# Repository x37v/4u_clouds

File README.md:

# 4u_clouds
a 4u layout for the mutable instrument's clouds, with added SD capability?

http://mutable-instruments.net/modules/clouds/open

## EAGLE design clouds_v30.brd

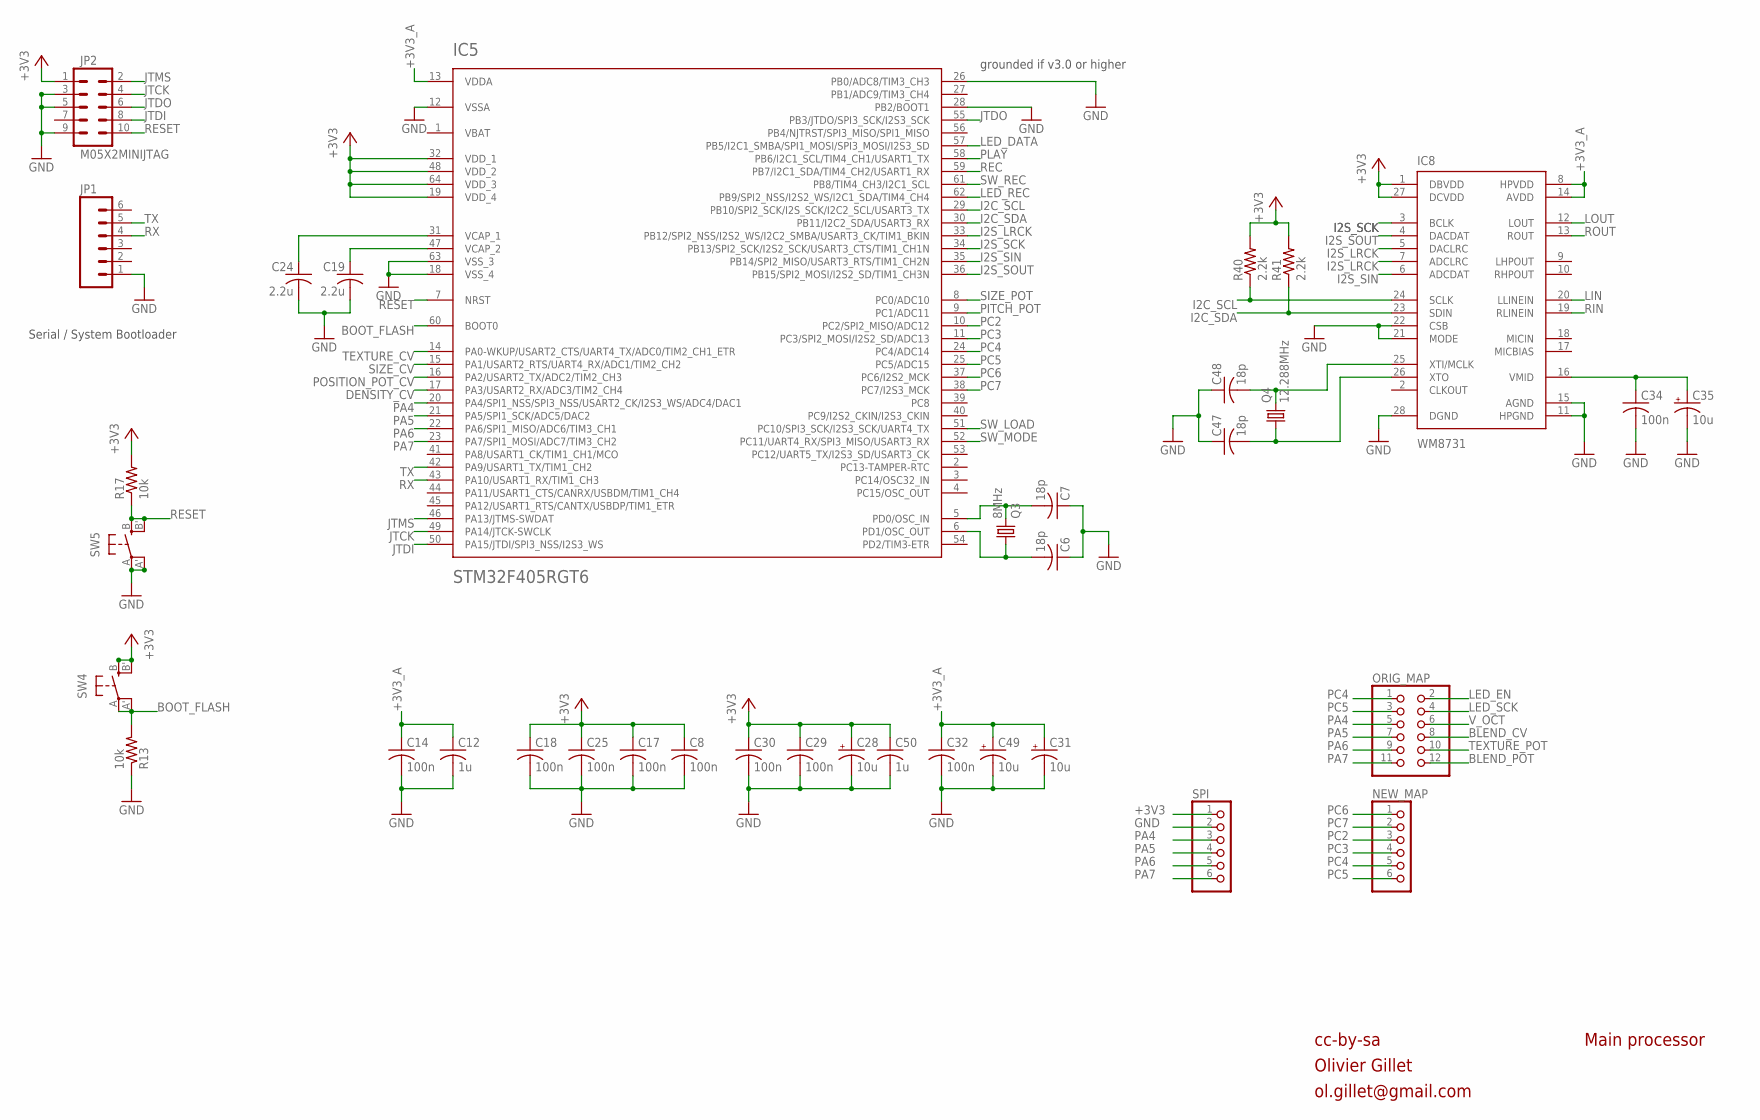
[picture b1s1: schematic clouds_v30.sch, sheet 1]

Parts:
C6, C7, C47, C48: 18p; C0603
C8, C14, C17, C18, C25, C29, C30, C32, C34: 100n; C0603
C12, C50: 1u; C0603
C19, C24: 2.2u; C0805
C28, C49: 10u; PANASONIC_A
C31, C35: 10u; PANASONIC_B
IC5: STM32F405RGT6; TQFP-10X10-64
IC8: WM8731; SSOP28
JP1: M06SIP; 1X06
JP2: M05X2MINIJTAG; 2X5-1.27
NEW_MAP: PINHD-1X6; 1X06
ORIG_MAP: PINHD-2X6; 2X06
Q3: 8MHz; HC49UP
Q4: 12.288MHz; HC49UP
R13, R17: 10k; R0603
R40, R41: 2.2k; R0603
SPI: PINHD-1X6; 1X06
SW4, SW5: EVQQ2; EVQ-Q2

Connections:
+3V3: C8.1, C17.1, C18.1, C25.1, C28.+, C29.1, C30.1, C50.1, IC5.19 (VDD_4), IC5.32 (VDD_1), IC5.48 (VDD_2), IC5.64 (VDD_3), IC8.1 (DBVDD), IC8.27 (DCVDD), JP2.1, R17.2, R40.2, R41.2, SPI.1, SW4.B (S), SW4.B' (S1); also elsewhere on the board
+3V3_A: C12.1, C14.1, C31.+, C32.1, C49.+, IC5.13 (VDDA), IC8.8 (HPVDD), IC8.14 (AVDD); also elsewhere on the board
BLEND_CV: ORIG_MAP.8; also elsewhere on the board
BLEND_POT: ORIG_MAP.12; also elsewhere on the board
BOOT_FLASH: IC5.60 (BOOT0), R13.2, SW4.A, SW4.A' (P1)
DENSITY_CV: IC5.17 (PA3/USART2_RX/ADC3/TIM2_CH4); also elsewhere on the board
GND: C6.1, C7.1, C8.2, C12.2, C14.2, C17.2, C18.2, C19.2, C24.2, C25.2, C28.-, C29.2, C30.2, C31.-, C32.2, C34.2, C35.-, C47.1, C48.1, C49.-, C50.2, IC5.12 (VSSA), IC5.18 (VSS_4), IC5.26 (PB0/ADC8/TIM3_CH3), IC5.28 (PB2/BOOT1), IC5.63 (VSS_3), IC8.11 (HPGND), IC8.15 (AGND), IC8.21 (MODE), IC8.22 (CSB), IC8.28 (DGND), JP1.1, JP2.3, JP2.5, JP2.9, R13.1, SPI.2, SW5.A, SW5.A' (P1); also elsewhere on the board
I2C_SCL: IC5.29 (PB10/SPI2_SCK/I2S_SCK/I2C2_SCL/USART3_TX), IC8.24 (SCLK), R40.1
I2C_SDA: IC5.30 (PB11/I2C2_SDA/USART3_RX), IC8.23 (SDIN), R41.1
I2S_LRCK: IC5.33 (PB12/SPI2_NSS/I2S2_WS/I2C2_SMBA/USART3_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), IC8.5 (DACLRC), IC8.7 (ADCLRC)
I2S_SCK: IC5.34 (PB13/SPI2_SCK/I2S2_SCK/USART3_CTS/TIM1_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), IC8.3 (BCLK)
I2S_SIN: IC5.35 (PB14/SPI2_MISO/USART3_RTS/TIM1_CH2N), IC8.6 (ADCDAT)
I2S_SOUT: IC5.36 (PB15/SPI2_MOSI/I2S2_SD/TIM1_CH3N), IC8.4 (DACDAT)
JTCK: IC5.49 (PA14/JTCK-SWCLK), JP2.4
JTDI: IC5.50 (PA15/JTDI/SPI3_NSS/I2S3_WS), JP2.8
JTDO: IC5.55 (PB3/JTDO/SPI3_SCK/I2S3_SCK), JP2.6
JTMS: IC5.46 (PA13/JTMS-SWDAT), JP2.2
LED_DATA: IC5.57 (PB5/I2C1_SMBA/SPI1_MOSI/SPI3_MOSI/I2S3_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); also elsewhere on the board
LED_EN: ORIG_MAP.2; also elsewhere on the board
LED_REC: IC5.62 (PB9/SPI2_NSS/I2S2_WS/I2C1_SDA/TIM4_CH4); also elsewhere on the board
LED_SCK: ORIG_MAP.4; also elsewhere on the board
LIN: IC8.20 (LLINEIN); also elsewhere on the board
LOUT: IC8.12 (LOUT); also elsewhere on the board
unnamed: C7.2, IC5.5 (PD0/OSC_IN), Q3.2
unnamed: C6.2, IC5.6 (PD1/OSC_OUT), Q3.1
unnamed: C19.1, IC5.47 (VCAP_2)
unnamed: C34.1, C35.+, IC8.16 (VMID)
unnamed: C24.1, IC5.31 (VCAP_1)
unnamed: C47.2, IC8.26 (XTO), Q4.1
unnamed: C48.2, IC8.25 (XTI/MCLK), Q4.2
PA4: IC5.20 (PA4/SPI1_NSS/SPI3_NSS/USART2_CK/I2S3_WS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), ORIG_MAP.5, SPI.3
PA5: IC5.21 (PA5/SPI1_SCK/ADC5/DAC2), ORIG_MAP.7, SPI.4
PA6: IC5.22 (PA6/SPI1_MISO/ADC6/TIM3_CH1), ORIG_MAP.9, SPI.5
PA7: IC5.23 (PA7/SPI1_MOSI/ADC7/TIM3_CH2), ORIG_MAP.11, SPI.6
PC2: IC5.10 (PC2/SPI2_MISO/ADC12), NEW_MAP.3
PC3: IC5.11 (PC3/SPI2_MOSI/I2S2_SD/ADC13), NEW_MAP.4
PC4: IC5.24 (PC4/ADC14), NEW_MAP.5, ORIG_MAP.1
PC5: IC5.25 (PC5/ADC15), NEW_MAP.6, ORIG_MAP.3
PC6: IC5.37 (PC6/I2S2_MCK), NEW_MAP.1
PC7: IC5.38 (PC7/I2S3_MCK), NEW_MAP.2
PITCH_POT: IC5.9 (PC1/ADC11); also elsewhere on the board
PLAY: IC5.58 (PB6/I2C1_SCL/TIM4_CH1/USART1_TX); also elsewhere on the board
POSITION_POT_CV: IC5.16 (PA2/USART2_TX/ADC2/TIM2_CH3); also elsewhere on the board
REC: IC5.59 (PB7/I2C1_SDA/TIM4_CH2/USART1_RX); also elsewhere on the board
RESET: IC5.7 (NRST), JP2.10, R17.1, SW5.B (S), SW5.B' (S1)
RIN: IC8.19 (RLINEIN); also elsewhere on the board
ROUT: IC8.13 (ROUT); also elsewhere on the board
RX: IC5.43 (PA10/USART1_RX/TIM1_CH3), JP1.4
SIZE_CV: IC5.15 (PA1/USART2_RTS/UART4_RX/ADC1/TIM2_CH2); also elsewhere on the board
SIZE_POT: IC5.8 (PC0/ADC10); also elsewhere on the board
SW_LOAD: IC5.51 (PC10/SPI3_SCK/I2S3_SCK/UART4_TX); also elsewhere on the board
SW_MODE: IC5.52 (PC11/UART4_RX/SPI3_MISO/USART3_RX); also elsewhere on the board
SW_REC: IC5.61 (PB8/TIM4_CH3/I2C1_SCL); also elsewhere on the board
TEXTURE_CV: IC5.14 (PA0-WKUP/USART2_CTS/UART4_TX/ADC0/TIM2_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); also elsewhere on the board
TEXTURE_POT: ORIG_MAP.10; also elsewhere on the board
TX: IC5.42 (PA9/USART1_TX/TIM1_CH2), JP1.5
VBAT: IC5.1 (VBAT)
V_OCT: ORIG_MAP.6; also elsewhere on the board

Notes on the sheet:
cc-by-sa
Olivier Gillet
ol.gillet@gmail.com
Main processor
Serial / System Bootloader
grounded if v3.0 or higher

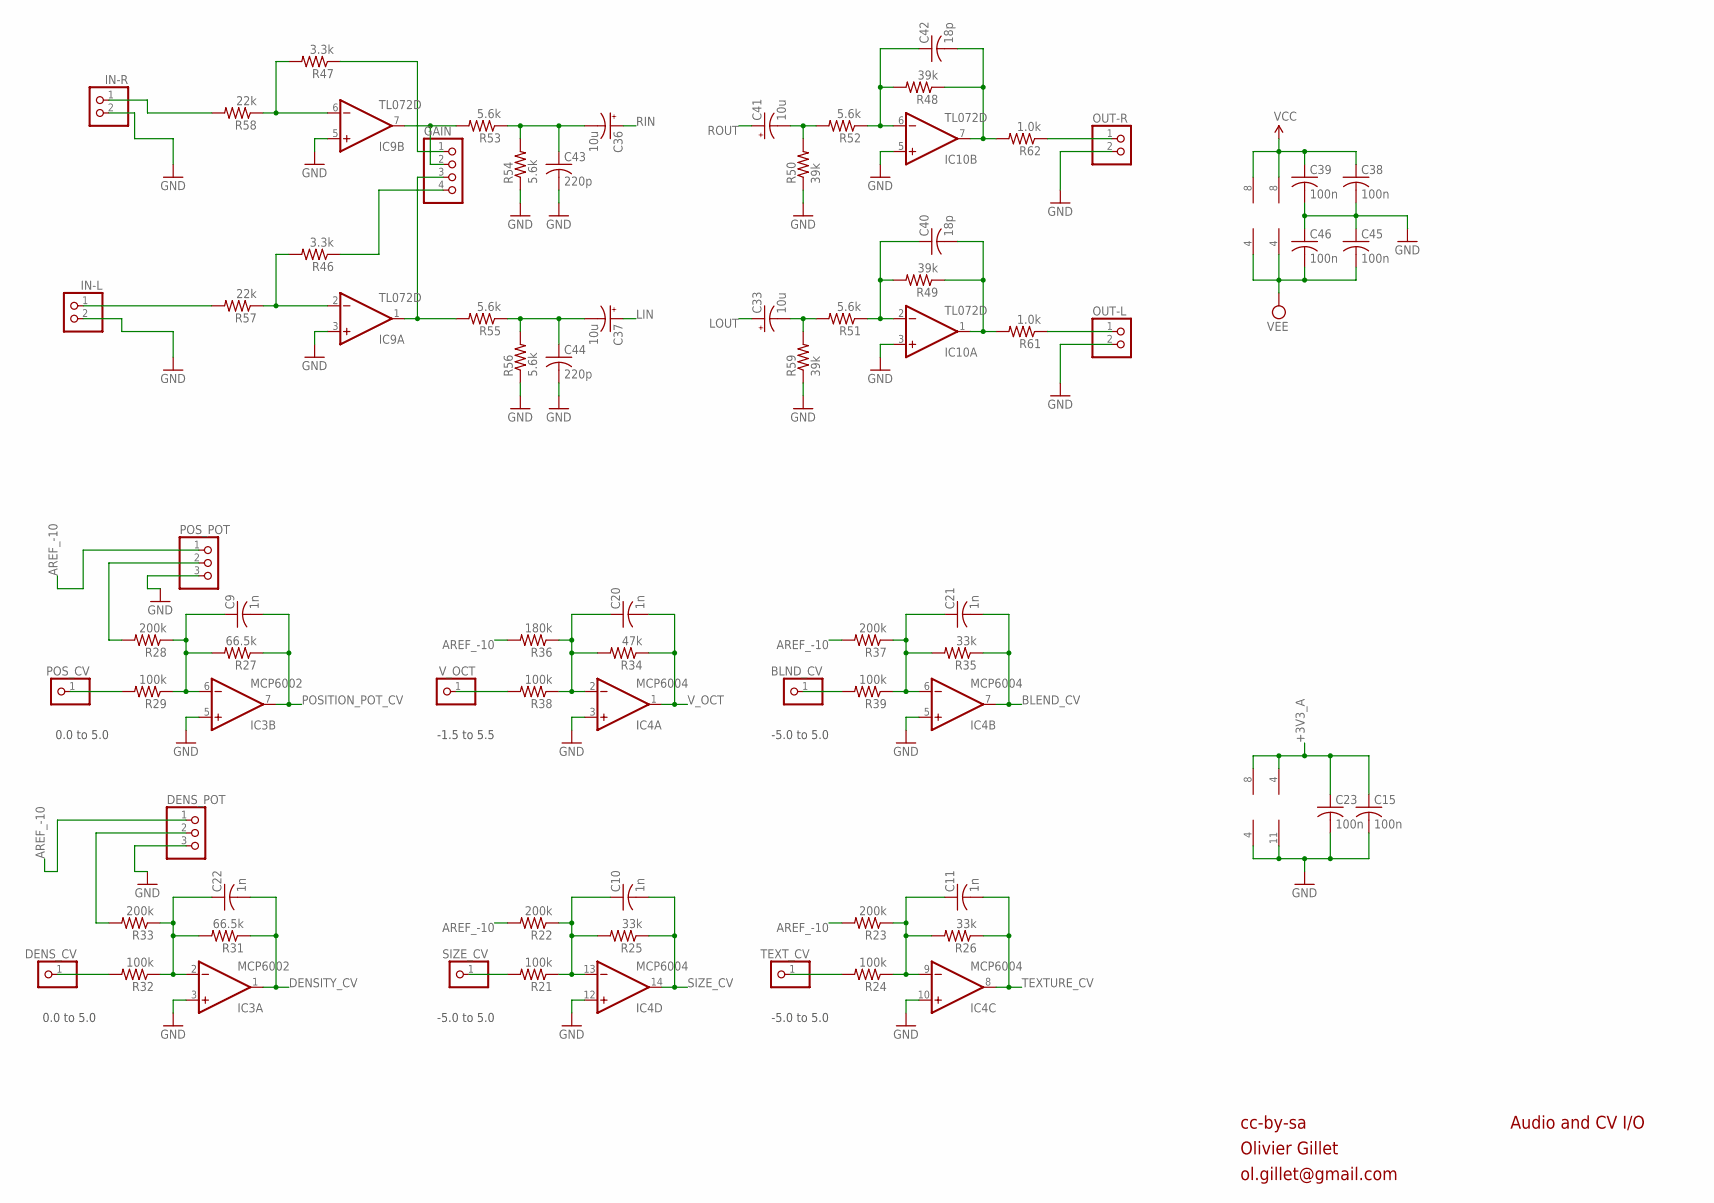
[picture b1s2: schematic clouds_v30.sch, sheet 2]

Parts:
BLND_CV: PINHD-1X1; 1X01
C9, C10, C11, C20, C21, C22: 1n; C0603
C15, C23, C38, C39, C45, C46: 100n; C0603
C33, C36, C37, C41: 10u; PANASONIC_B
C40, C42: 18p; C0603
C43, C44: 220p; C0603
DENS_CV: PINHD-1X1; 1X01
DENS_POT: PINHD-1X3; 1X03
GAIN: PINHD-1X4; 1X04
IC3: MCP6002; SO08
IC4: MCP6004; SO14
IC9, IC10: TL072D; SO08
IN-L: PINHD-1X2; 1X02
IN-R: PINHD-1X2; 1X02
OUT-L: PINHD-1X2; 1X02
OUT-R: PINHD-1X2; 1X02
POS_CV: PINHD-1X1; 1X01
POS_POT: PINHD-1X3; 1X03
R21, R24, R29, R32, R38, R39: 100k; R0603
R22, R23, R28, R33, R37: 200k; R0603
R25, R26, R35: 33k; R0603
R27, R31: 66.5k; R0603
R34: 47k; R0603
R36: 180k; R0603
R46, R47: 3.3k; R0603
R48, R49, R50, R59: 39k; R0603
R51, R52, R53, R54, R55, R56: 5.6k; R0603
R57, R58: 22k; R0603
R61, R62: 1.0k; R0603
SIZE_CV: PINHD-1X1; 1X01
TEXT_CV: PINHD-1X1; 1X01
V_OCT: PINHD-1X1; 1X01

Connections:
+3V3_A: C15.1, C23.1, IC3.8 (V+), IC4.4 (V+); also elsewhere on the board
AREF_-10: DENS_POT.1, POS_POT.1, R22.2, R23.2, R36.2, R37.2; also elsewhere on the board
BLEND_CV: C21.2, IC4.7 (OUT), R35.1; also elsewhere on the board
DENSITY_CV: C22.2, IC3.1 (OUT), R31.1; also elsewhere on the board
GND: C15.2, C23.2, C38.2, C39.2, C43.2, C44.2, C45.1, C46.1, DENS_POT.3, IC3.3 (+IN), IC3.4 (V-), IC3.5 (+IN), IC4.3 (+IN), IC4.5 (+IN), IC4.10 (+IN), IC4.11 (V-), IC4.12 (+IN), IC9.3 (+IN), IC9.5 (+IN), IC10.3 (+IN), IC10.5 (+IN), IN-L.2, IN-R.2, OUT-L.2, OUT-R.2, POS_POT.3, R50.1, R54.1, R56.1, R59.1; also elsewhere on the board
LIN: C37.+; also elsewhere on the board
LOUT: C33.+; also elsewhere on the board
LOUT_JACK: OUT-L.1, R61.1
unnamed: R21.2, SIZE_CV.1
unnamed: C10.1, IC4.13 (-IN), R21.1, R22.1, R25.2
unnamed: R24.2, TEXT_CV.1
unnamed: C11.1, IC4.9 (-IN), R23.1, R24.1, R26.2
unnamed: BLND_CV.1, R39.2
unnamed: R38.2, V_OCT.1
unnamed: C20.1, IC4.2 (-IN), R34.2, R36.1, R38.1
unnamed: DENS_CV.1, R32.2
unnamed: C21.1, IC4.6 (-IN), R35.2, R37.1, R39.1
unnamed: C37.-, C44.1, R55.1, R56.2
unnamed: IN-R.1, R58.2
unnamed: IN-L.1, R57.2
unnamed: C36.-, C43.1, R53.1, R54.2
unnamed: C41.-, R50.2, R52.2
unnamed: C22.1, IC3.2 (-IN), R31.2, R32.1, R33.1
unnamed: C42.1, IC10.6 (-IN), R48.2, R52.1
unnamed: DENS_POT.2, R33.2
unnamed: POS_CV.1, R29.2
unnamed: C42.2, IC10.7 (OUT), R48.1, R62.2
unnamed: C9.1, IC3.6 (-IN), R27.2, R28.1, R29.1
unnamed: C33.-, R51.2, R59.2
unnamed: C40.1, IC10.2 (-IN), R49.2, R51.1
unnamed: C40.2, IC10.1 (OUT), R49.1, R61.2
unnamed: POS_POT.2, R28.2
unnamed: GAIN.2, IC9.7 (OUT), R53.2
unnamed: GAIN.3, IC9.1 (OUT), R55.2
unnamed: GAIN.1, R47.1
unnamed: GAIN.4, R46.1
unnamed: IC9.6 (-IN), R47.2, R58.1
unnamed: IC9.2 (-IN), R46.2, R57.1
POSITION_POT_CV: C9.2, IC3.7 (OUT), R27.1; also elsewhere on the board
RIN: C36.+; also elsewhere on the board
ROUT: C41.+; also elsewhere on the board
ROUT_JACK: OUT-R.1, R62.1
SIZE_CV: C10.2, IC4.14 (OUT), R25.1; also elsewhere on the board
TEXTURE_CV: C11.2, IC4.8 (OUT), R26.1; also elsewhere on the board
VCC: C38.1, C39.1, IC9.8 (V+), IC10.8 (V+); also elsewhere on the board
VEE: C45.2, C46.2, IC9.4 (V-), IC10.4 (V-); also elsewhere on the board
V_OCT: C20.2, IC4.1 (OUT), R34.1; also elsewhere on the board

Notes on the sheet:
cc-by-sa
Olivier Gillet
ol.gillet@gmail.com
Audio and CV I/O
0.0 to 5.0
-1.5 to 5.5
-5.0 to 5.0

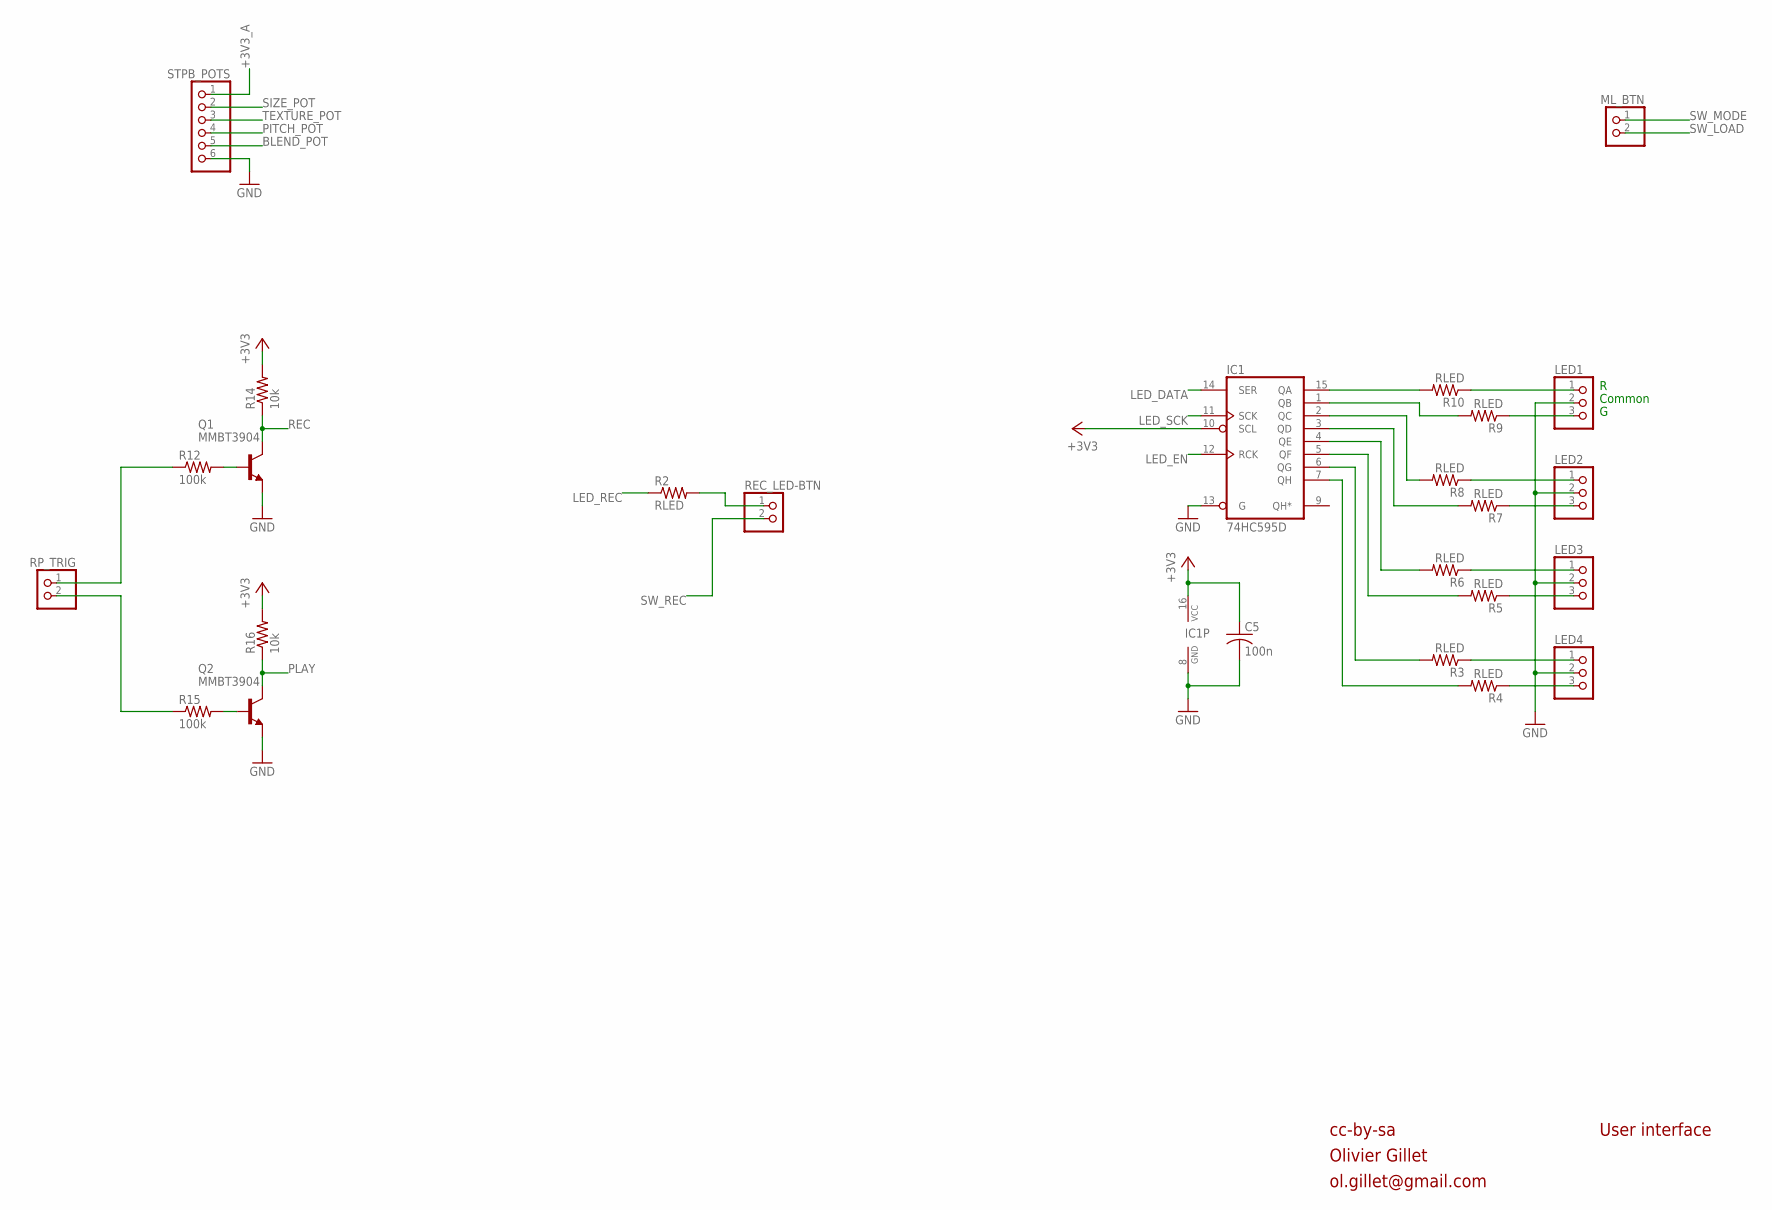
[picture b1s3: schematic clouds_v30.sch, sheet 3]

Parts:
C5: 100n; C0603
IC1: 74HC595D; SO16
LED1, LED2, LED3, LED4: PINHD-1X3; 1X03
ML_BTN: PINHD-1X2; 1X02
Q1, Q2: MMBT3904; SOT23-BEC
R2, R3, R4, R5, R6, R7, R8, R9, R10: RLED; R0603
R12, R15: 100k; R0603
R14, R16: 10k; R0603
REC_LED-BTN: PINHD-1X2; 1X02
RP_TRIG: PINHD-1X2; 1X02
STPB_POTS: PINHD-1X6; 1X06

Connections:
+3V3: C5.1, IC1.10 (SCL), IC1.16 (VCC), R14.2, R16.2; also elsewhere on the board
+3V3_A: STPB_POTS.1; also elsewhere on the board
BLEND_POT: STPB_POTS.5; also elsewhere on the board
GND: C5.2, IC1.8 (GND), IC1.13 (G), LED1.2, LED2.2, LED3.2, LED4.2, Q1.E, Q2.E, STPB_POTS.6; also elsewhere on the board
LED_DATA: IC1.14 (SER); also elsewhere on the board
LED_EN: IC1.12 (RCK); also elsewhere on the board
LED_REC: R2.1; also elsewhere on the board
LED_SCK: IC1.11 (SCK); also elsewhere on the board
unnamed: LED1.3, R9.1
unnamed: LED1.1, R10.1
unnamed: LED2.1, R8.1
unnamed: LED2.3, R7.1
unnamed: LED3.1, R6.1
unnamed: R15.1, RP_TRIG.2
unnamed: Q2.B, R15.2
unnamed: R2.2, REC_LED-BTN.1
unnamed: LED3.3, R5.1
unnamed: LED4.1, R3.1
unnamed: LED4.3, R4.1
unnamed: IC1.15 (QA), R10.2
unnamed: IC1.1 (QB), R9.2
unnamed: IC1.2 (QC), R8.2
unnamed: IC1.3 (QD), R7.2
unnamed: IC1.4 (QE), R6.2
unnamed: IC1.5 (QF), R5.2
unnamed: IC1.6 (QG), R3.2
unnamed: IC1.7 (QH), R4.2
unnamed: R12.1, RP_TRIG.1
unnamed: Q1.B, R12.2
PITCH_POT: STPB_POTS.4; also elsewhere on the board
PLAY: Q2.C, R16.1; also elsewhere on the board
REC: Q1.C, R14.1; also elsewhere on the board
SIZE_POT: STPB_POTS.2; also elsewhere on the board
SW_LOAD: ML_BTN.2; also elsewhere on the board
SW_MODE: ML_BTN.1; also elsewhere on the board
SW_REC: REC_LED-BTN.2; also elsewhere on the board
TEXTURE_POT: STPB_POTS.3; also elsewhere on the board

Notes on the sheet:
cc-by-sa
Olivier Gillet
ol.gillet@gmail.com
User interface
Common

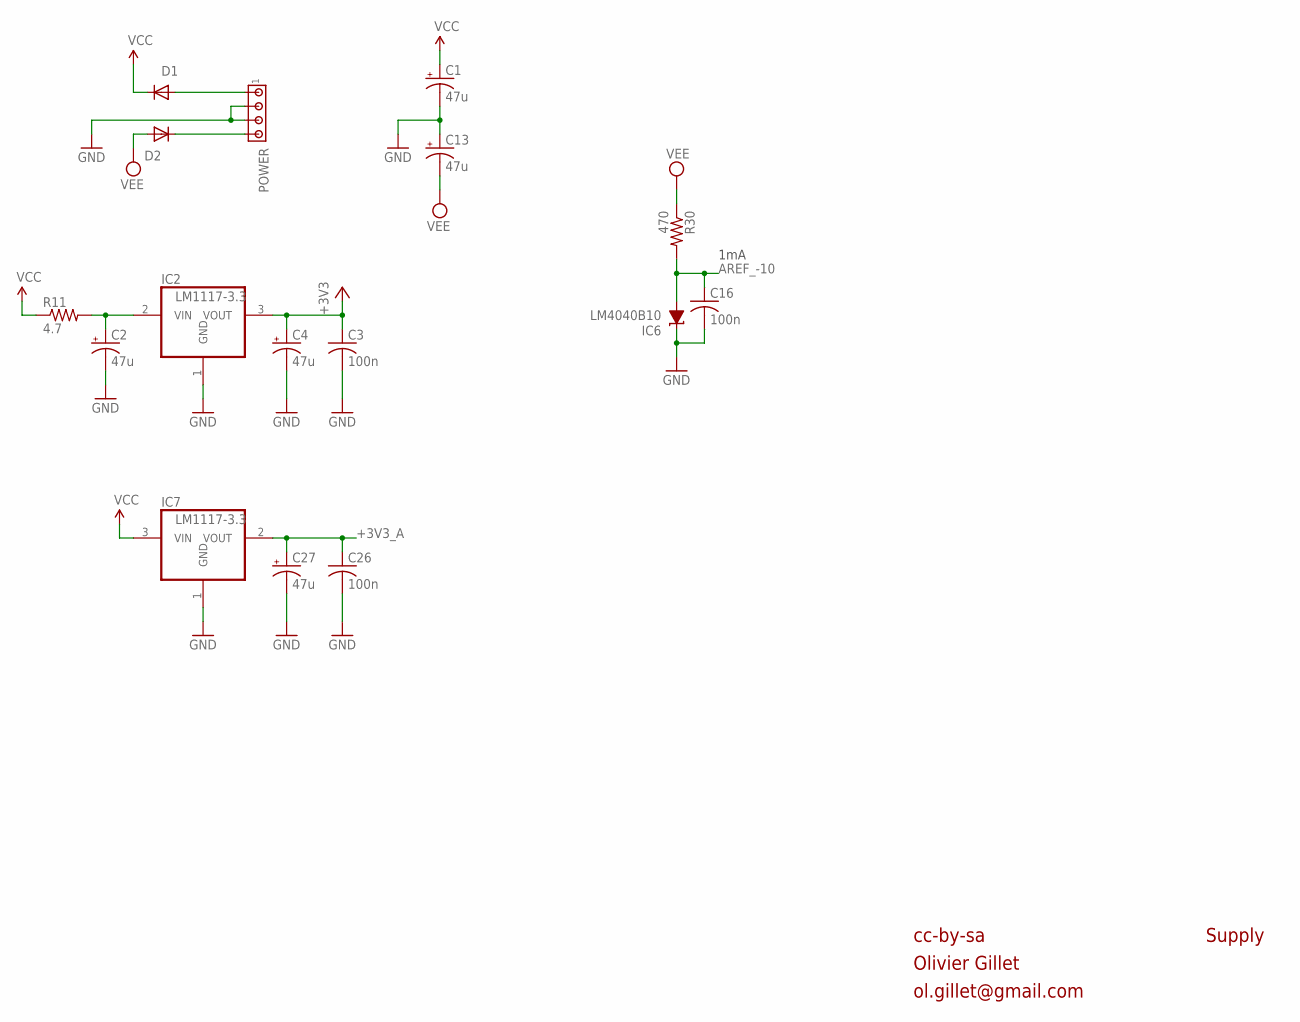
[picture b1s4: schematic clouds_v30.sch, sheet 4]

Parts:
C1, C2, C4, C13, C27: 47u; PANASONIC_D
C3, C16, C26: 100n; C0603
D1, D2: 1N5819HW; SOD123
IC2: LM1117-3.3; TO252
IC6: LM4040B10; DBZ_R-PDSO-G3
IC7: LM1117-3.3; SOT223
POWER: MTA04-156; 1X4MTA
R11: 4.7; R1206
R30: 470; R0603

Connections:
+3V3: C3.1, C4.+, IC2.3 (VOUT); also elsewhere on the board
+3V3_A: C26.1, C27.+, IC7.2 (VOUT); also elsewhere on the board
AREF_-10: C16.1, IC6.2 (A), R30.2; also elsewhere on the board
GND: C1.-, C2.-, C3.2, C4.-, C13.+, C16.2, C26.2, C27.-, IC2.1 (GND), IC6.1 (C), IC7.1 (GND), POWER.2, POWER.3; also elsewhere on the board
unnamed: C2.+, IC2.2 (VIN), R11.2
unnamed: D1.A, POWER.1
unnamed: D2.C, POWER.4
VCC: C1.+, D1.C, IC7.3 (VIN), R11.1; also elsewhere on the board
VEE: C13.-, D2.A, R30.1; also elsewhere on the board

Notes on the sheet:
1mA
cc-by-sa
Olivier Gillet
ol.gillet@gmail.com
Supply

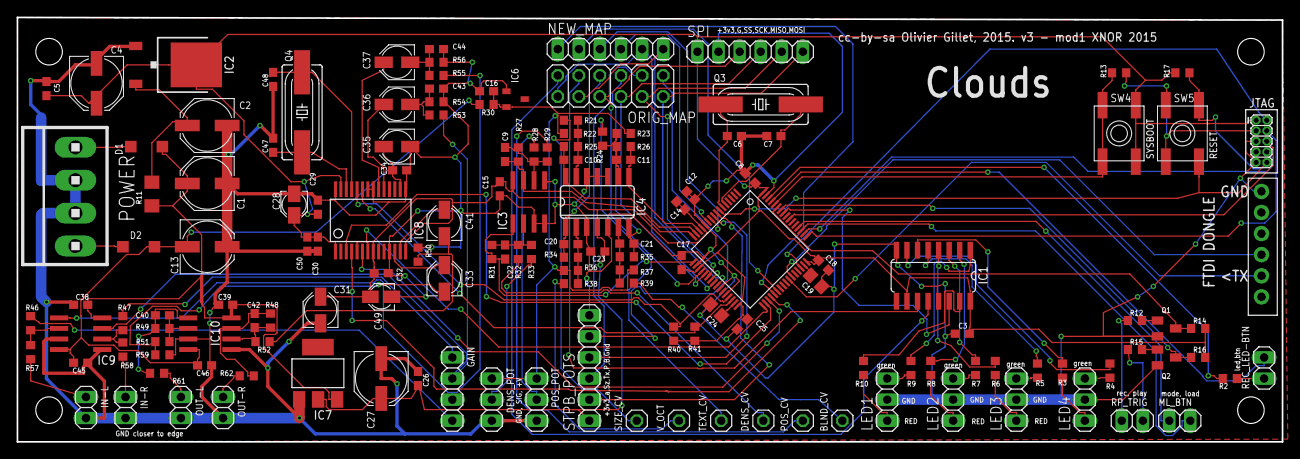
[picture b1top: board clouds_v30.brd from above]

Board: 2 copper layers, 152.4 x 51.1 mm, 148 parts (1 on the bottom side), 116 nets.

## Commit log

2015-12-29 clouds layed out for 4u, modded for possible SD, unrouted
2015-12-29 ignores
2015-12-29 moved some stuff around on brd
2015-12-29 moving stuff around, think i should move the i2s interface
2015-12-29 moved i2s closer to audio i/o
2015-12-29 about to route
2015-12-29 leds mostly routed
2015-12-30 more routing!
2015-12-30 lots more hand routing
2015-12-30 auto routed + some fixup, still some to do
2015-12-30 almost all routed!
2015-12-30 more routing! GRNDS!!!
2015-12-30 everything is routed except a few grounds i think!
2015-12-30 completely routed!!! [i think, some weird unrouted stuff under pads]
2015-12-30 added a bunch more documentation
2015-12-30 moved some text around

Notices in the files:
clouds_v30.brd:
cc-by-sa Olivier Gillet, 2015. v3 - mod1 XNOR 2015
